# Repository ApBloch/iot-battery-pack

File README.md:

# iot-battery-pack
Design for a 3s iot battery pack with balance charging.

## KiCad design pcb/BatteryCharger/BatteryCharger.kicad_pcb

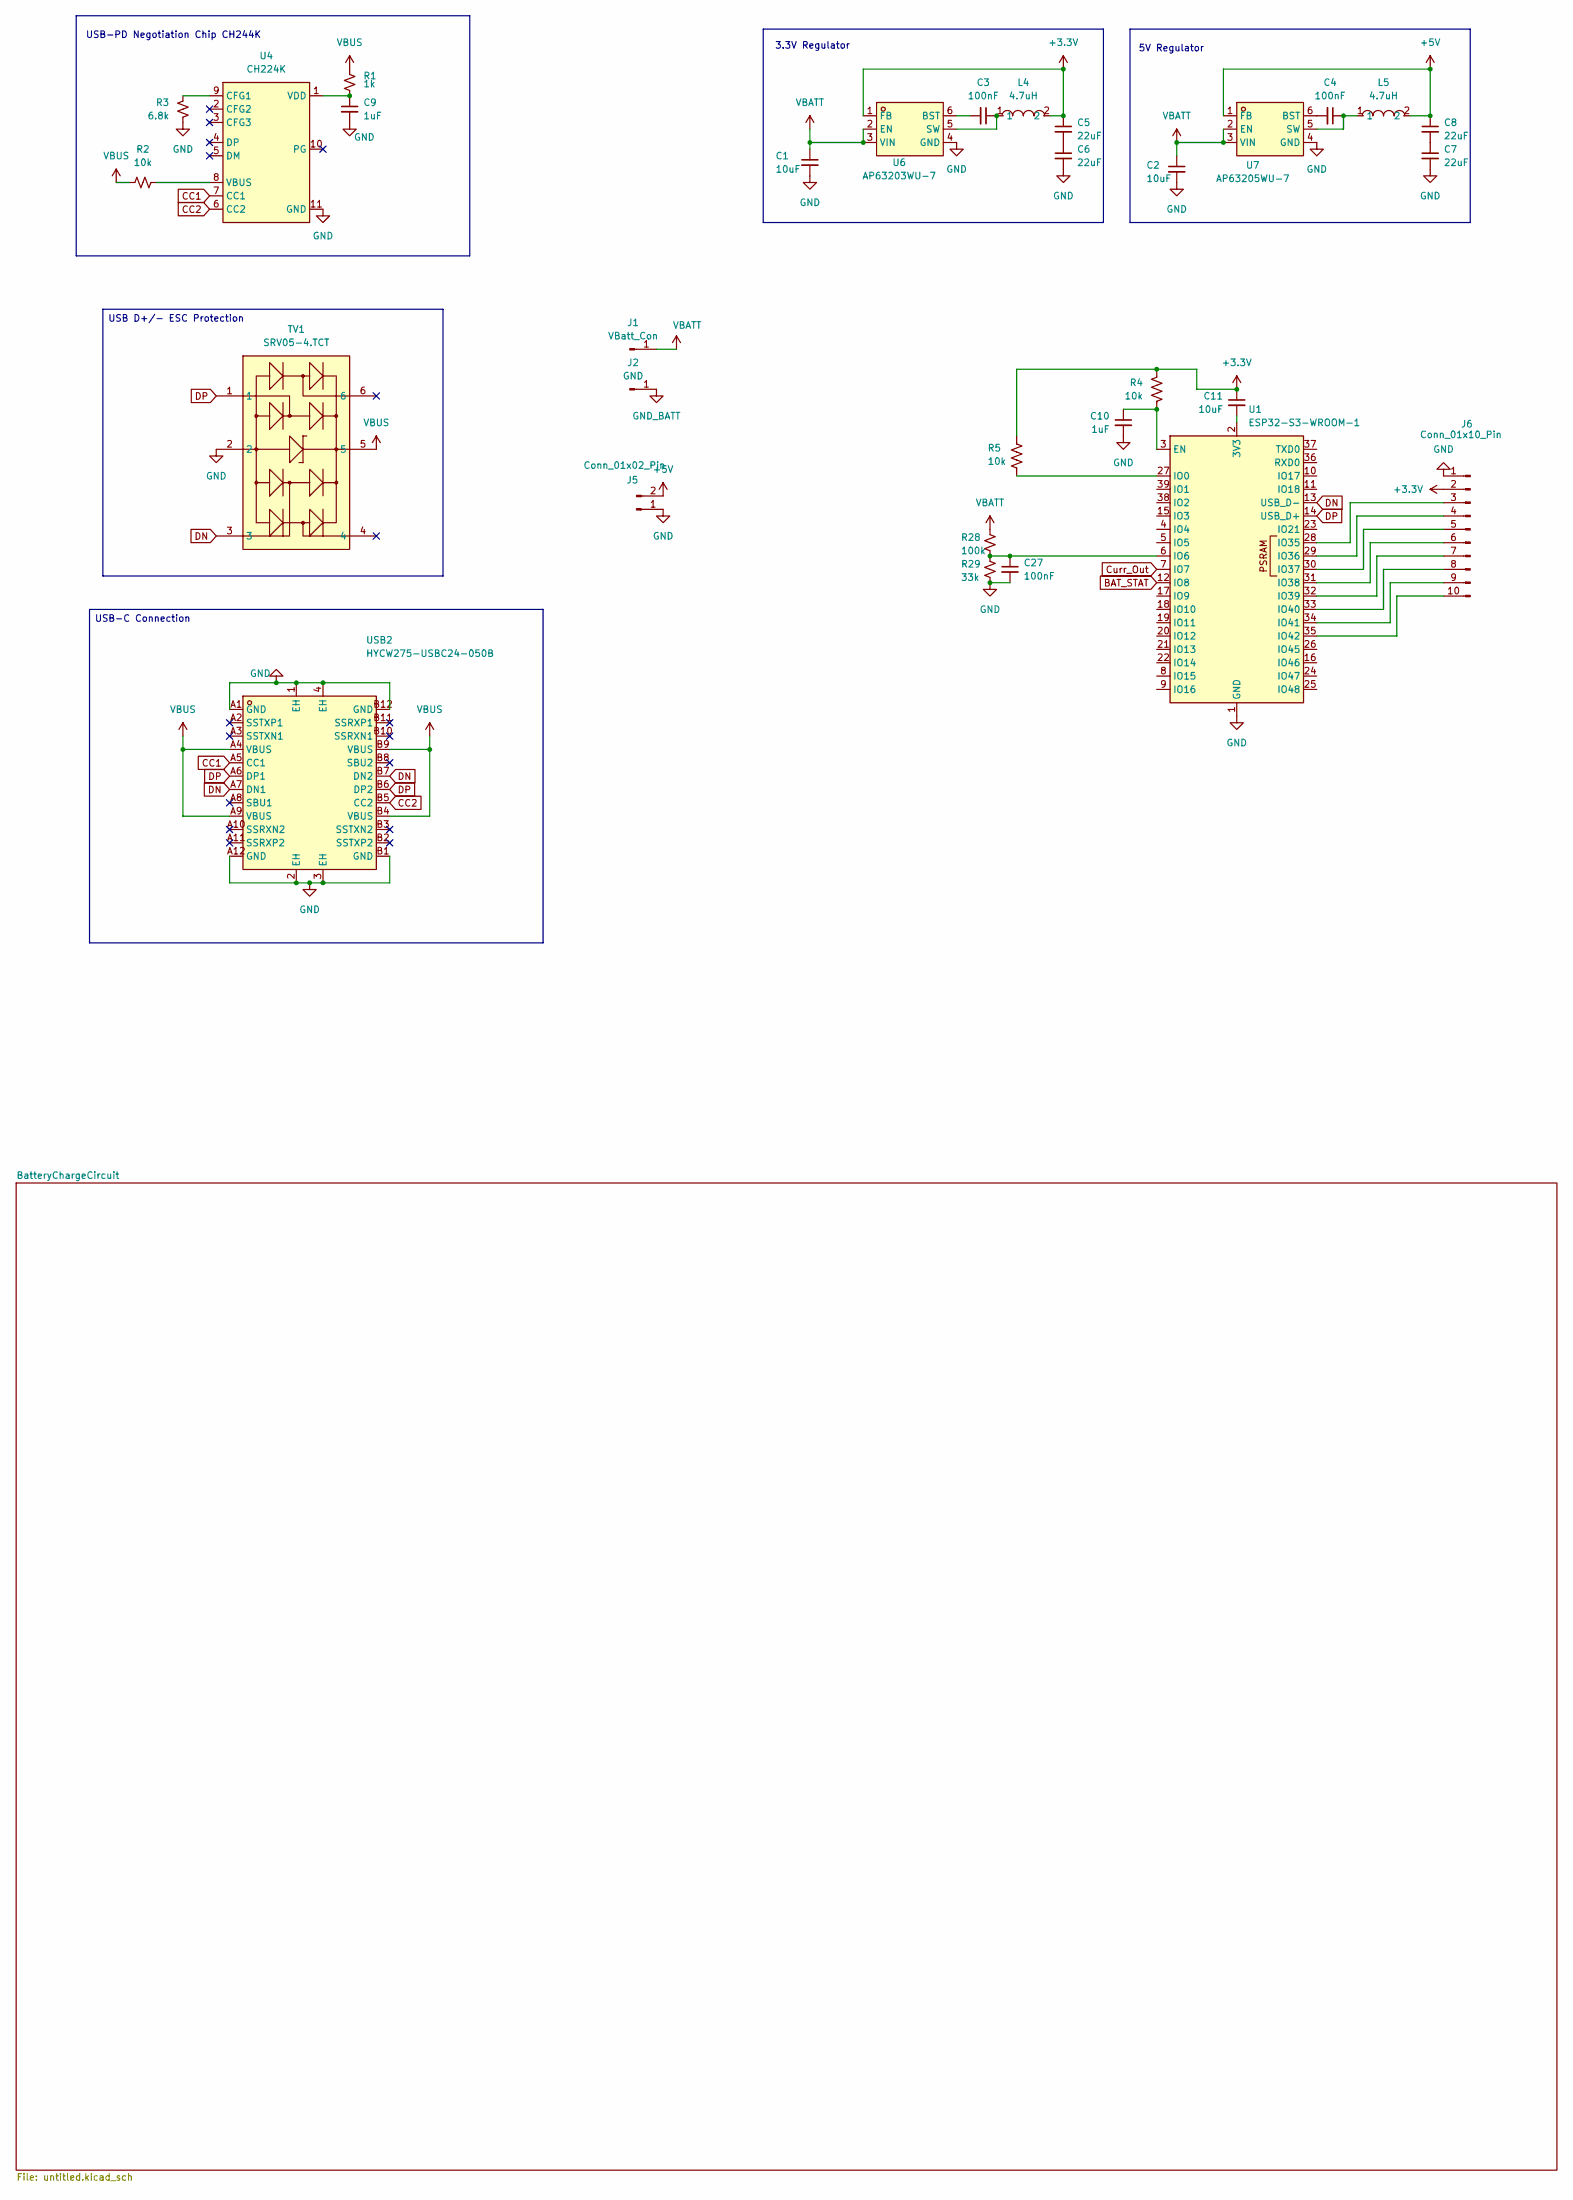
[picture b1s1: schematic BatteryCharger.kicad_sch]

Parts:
C1, C2, C11: 10uF; C_0603_1608Metric
C3, C4, C27: 100nF; C_0603_1608Metric
C5, C6, C7, C8: 22uF; C_0603_1608Metric
C9, C10: 1uF; C_0603_1608Metric
J1: VBatt_Con; TestPoint_THTPad_D4.0mm_Drill2.0mm
J2: GND; TestPoint_THTPad_4.0x4.0mm_Drill2.0mm
J5: Conn_01x02_Pin; PinHeader_1x02_P2.00mm_Vertical
J6: Conn_01x10_Pin; PinHeader_1x10_P2.54mm_Vertical
L4, L5: 4.7uH; IND-SMD_L5.7-W5.2_CYA0530; MPN CYA0520-4.7UH; LCSC Part C19274357
R1: 1k; R_0603_1608Metric
R2, R4, R5: 10k; R_0603_1608Metric
R3: 6.8k; R_0603_1608Metric
R28: 100k; R_0603_1608Metric
R29: 33k; R_0603_1608Metric
TV1: SRV05-4.TCT; SOT-23-6_L2.9-W1.6-P0.95-LS2.8-BR; MPN SRV05-4.TCT; LCSC Part C13612
U1: ESP32-S3-WROOM-1
U4: CH224K; ESSOP-10_L4.9-W3.9-P1.0-LS6.0-TL-EP; MPN CH224K; LCSC Part C970725
U6: AP63203WU-7; TSOT-26_L2.9-W1.6-P0.95-LS2.8-BL; MPN AP63203WU-7; LCSC Part C780769
U7: AP63205WU-7; TSOT-23-6_L2.9-W1.6-P0.95-LS2.8-BL; MPN AP63205WU-7; LCSC Part C2071056
USB2: HYCW275-USBC24-050B; USB-C-SMD_HYCW275-USBC24-050B; MPN HYCW275-USBC24-050B; LCSC Part C42400261

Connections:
+3.3V: C5.1, C11.1, J6.2, L4.2, R4.1, R5.1, U6.1 (FB); also elsewhere on the board
+5V: C8.1, J5.2, L5.2, U7.1 (FB)
BAT_STAT: U1.12 (IO8); also elsewhere on the board
CC1: U4.7 (CC1), USB2.A5 (CC1)
CC2: U4.6 (CC2), USB2.B5 (CC2)
Cell2_+: C1.1, C2.1, J1.1 (Pin_1_1), R28.1, U6.2 (EN), U6.3 (VIN), U7.2 (EN), U7.3 (VIN); also elsewhere on the board
Curr_Out: U1.7 (IO7); also elsewhere on the board
DN: TV1.3, U1.13 (USB_D-), USB2.A7 (DN1), USB2.B7 (DN2)
DP: TV1.1, U1.14 (USB_D+), USB2.A6 (DP1), USB2.B6 (DP2)
GND: C1.2, C2.2, C6.2, C7.2, C9.2, C10.2, C27.2, J5.1, J6.1, R3.2, R29.2, TV1.2, U1.1 (GND), U1.40 (GND), U1.41 (GND), U4.11 (GND), U6.4 (GND), U7.4 (GND), USB2.0, USB2.1 (EH), USB2.2 (EH), USB2.3 (EH), USB2.4 (EH), USB2.A1 (GND), USB2.A12 (GND), USB2.B1 (GND), USB2.B12 (GND); also elsewhere on the board
GND_BATT: J2.1 (Pin_1_1); also elsewhere on the board
unnamed: C5.2, C6.1
unnamed: C7.1, C8.2
unnamed: J6.3, U1.28 (IO35)
unnamed: J6.4, U1.29 (IO36)
unnamed: J6.5, U1.30 (IO37)
unnamed: J6.6, U1.31 (IO38)
unnamed: J6.7, U1.32 (IO39)
unnamed: J6.8, U1.33 (IO40)
unnamed: J6.9, U1.34 (IO41)
unnamed: J6.10, U1.35 (IO42)
unnamed: C11.2, U1.2 (3V3)
unnamed: C10.1, R4.2, U1.3 (EN)
unnamed: R5.2, U1.27 (IO0)
unnamed: C27.1, R28.2, R29.1, U1.6 (IO6)
unnamed: R3.1, U4.9 (CFG1)
unnamed: R2.1, U4.8 (VBUS)
unnamed: C9.1, R1.2, U4.1 (VDD)
unnamed: C3.2, U6.6 (BST)
unnamed: C3.1, L4.1, U6.5 (SW)
unnamed: C4.2, U7.6 (BST)
unnamed: C4.1, L5.1, U7.5 (SW)
VBUS: R1.1, R2.2, TV1.5, USB2.A4 (VBUS), USB2.A9 (VBUS), USB2.B4 (VBUS), USB2.B9 (VBUS); also elsewhere on the board

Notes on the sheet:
USB-PD Negotiation Chip CH244K
3.3V Regulator
5V Regulator
USB D+/- ESC Protection
USB-C Connection

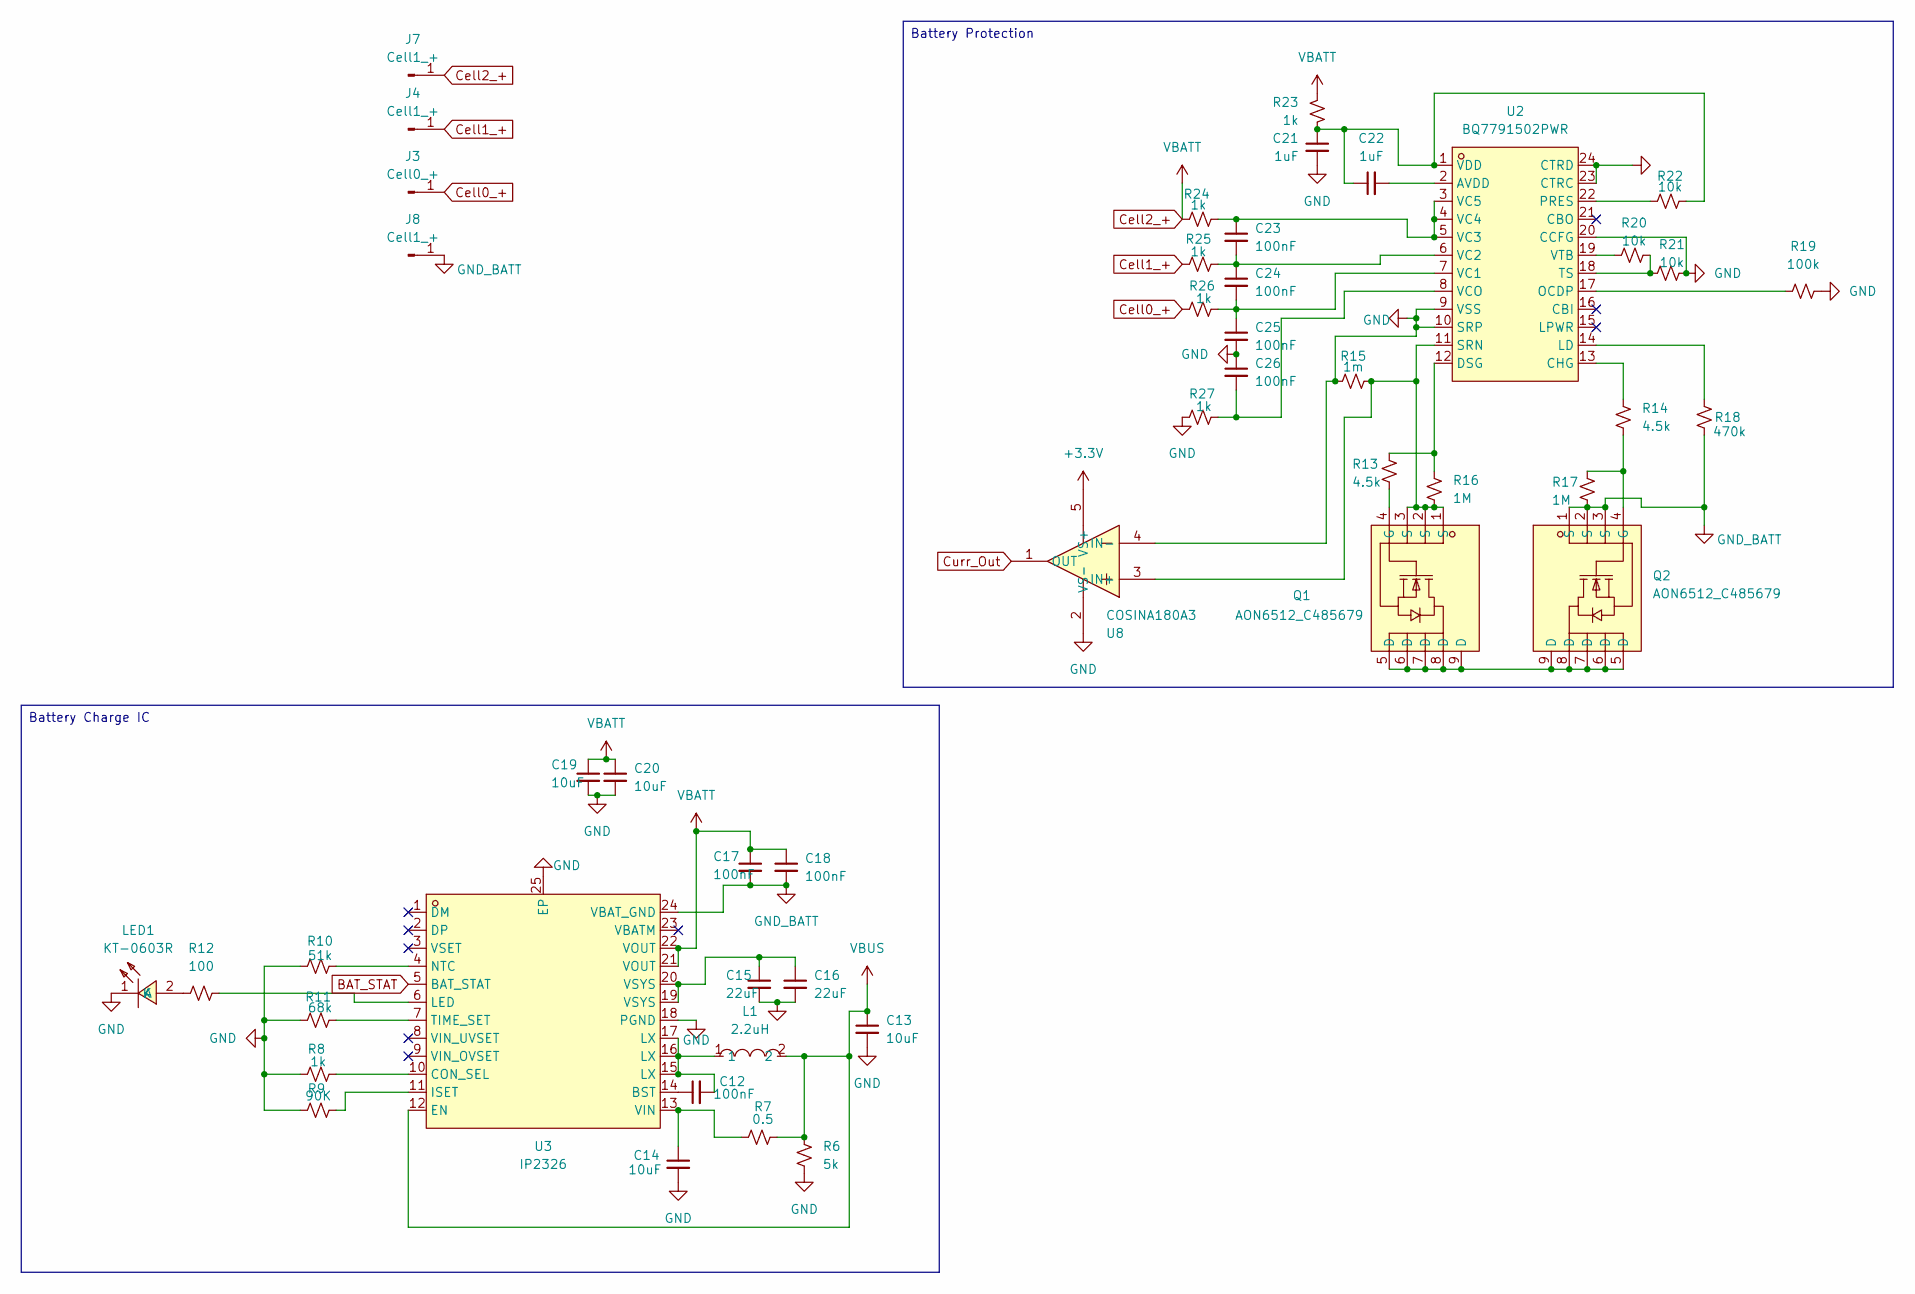
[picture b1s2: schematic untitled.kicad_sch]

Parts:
C12, C17, C18, C23, C24, C25, C26: 100nF; C_0603_1608Metric
C13, C14, C19, C20: 10uF; C_0603_1608Metric
C15, C16: 22uF; C_0603_1608Metric
C21, C22: 1uF; C_0603_1608Metric
J3: Cell0_+; TestPoint_Pad_D2.5mm
J4, J7, J8: Cell1_+; TestPoint_Pad_D2.5mm
L1: 2.2uH; IND-SMD_L5.0-W5.0; MPN CKCS5020-2.2uH/M; LCSC Part C354595
LED1: KT-0603R; LED0603-RD; MPN KT-0603R; LCSC Part C2286
Q1, Q2: AON6512_C485679; PDFN-8_L5.6-W5.2-P1.27-LS6.1-BL; MPN AON6512; LCSC Part C485679
R6: 5k; R_0603_1608Metric
R7: 0.5; R_0603_1608Metric
R8, R23, R24, R25, R26, R27: 1k; R_0603_1608Metric
R9: 90K; R_0603_1608Metric
R10: 51k; R_0603_1608Metric
R11: 68k; R_0603_1608Metric
R12: 100; R_0603_1608Metric
R13, R14: 4.5k; R_0603_1608Metric
R15: 1m; R_2512_6332Metric
R16, R17: 1M; R_0603_1608Metric
R18: 470k; R_0603_1608Metric
R19: 100k; R_0603_1608Metric
R20, R21, R22: 10k; R_0603_1608Metric
U2: BQ7791502PWR; TSSOP-24_L7.8-W4.4-P0.65-LS6.4-BL_1; MPN BQ7791502PWR; LCSC Part C2865574
U3: IP2326; VQFN-24_L4.0-W4.0-P0.50-BL-EP2.5; MPN IP2326; LCSC Part C2832094
U8: COSINA180A3; SOT-23-5_L2.9-W1.6-P0.95-LS2.8-BL; MPN COSINA180A3; LCSC Part C22392282

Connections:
+3.3V: U8.5 (VS+); also elsewhere on the board
BAT_STAT: U3.5 (BAT_STAT); also elsewhere on the board
Cell0_+: J3.1 (Pin_1_1), R26.1
Cell1_+: J4.1 (Pin_1_1), R25.1
Cell2_+: C17.1, C18.1, C19.1, C20.1, J7.1 (Pin_1_1), R23.1, R24.1, U3.21 (VOUT), U3.22 (VOUT); also elsewhere on the board
Curr_Out: U8.1 (OUT); also elsewhere on the board
GND: C13.2, C14.2, C15.2, C16.2, C19.2, C20.2, C21.2, C25.2, C26.1, LED1.1 (K), R6.2, R8.1, R9.1, R10.1, R11.1, R15.1, R19.2, R21.2, R27.1, U2.9 (VSS), U2.10 (SRP), U2.20 (CCFG), U2.23 (CTRC), U2.24 (CTRD), U3.18 (PGND), U3.25 (EP), U8.2 (VS-), U8.4 (IN-); also elsewhere on the board
GND_BATT: C17.2, C18.2, J8.1 (Pin_1_1), Q2.1 (S), Q2.2 (S), Q2.3 (S), R17.2, R18.1, U3.24 (VBAT_GND); also elsewhere on the board
unnamed: C12.2, L1.1, U3.15 (LX), U3.16 (LX), U3.17 (LX)
unnamed: C15.1, C16.1, U3.19 (VSYS), U3.20 (VSYS)
unnamed: LED1.2 (A), R12.1
unnamed: Q1.5 (D), Q1.6 (D), Q1.7 (D), Q1.8 (D), Q1.9 (D), Q2.5 (D), Q2.6 (D), Q2.7 (D), Q2.8 (D), Q2.9 (D)
unnamed: Q1.4 (G), R13.2
unnamed: Q2.4 (G), R14.2, R17.1
unnamed: C22.2, U2.2 (AVDD)
unnamed: R14.1, U2.13 (CHG)
unnamed: R13.1, R16.1, U2.12 (DSG)
unnamed: R18.2, U2.14 (LD)
unnamed: R19.1, U2.17 (OCDP)
unnamed: R22.1, U2.22 (PRES)
unnamed: Q1.1 (S), Q1.2 (S), Q1.3 (S), R15.2, R16.2, U2.11 (SRN), U8.3 (IN+)
unnamed: R20.2, R21.1, U2.18 (TS)
unnamed: C24.2, C25.1, R26.2, U2.7 (VC1)
unnamed: C23.2, C24.1, R25.2, U2.6 (VC2)
unnamed: C23.1, R24.2, U2.3 (VC5), U2.4 (VC4), U2.5 (VC3)
unnamed: C26.2, R27.2, U2.8 (VCO)
unnamed: C21.1, C22.1, R22.2, R23.2, U2.1 (VDD)
unnamed: R20.1, U2.19 (VTB)
unnamed: C12.1, U3.14 (BST)
unnamed: R8.2, U3.10 (CON_SEL)
unnamed: R9.2, U3.11 (ISET)
unnamed: R12.2, U3.6 (LED)
unnamed: R10.2, U3.4 (NTC)
unnamed: R11.2, U3.7 (TIME_SET)
unnamed: C14.1, R7.1, U3.13 (VIN)
VBUS: C13.1, L1.2, R6.1, R7.2, U3.12 (EN); also elsewhere on the board

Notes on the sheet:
Battery Protection
Battery Charge IC

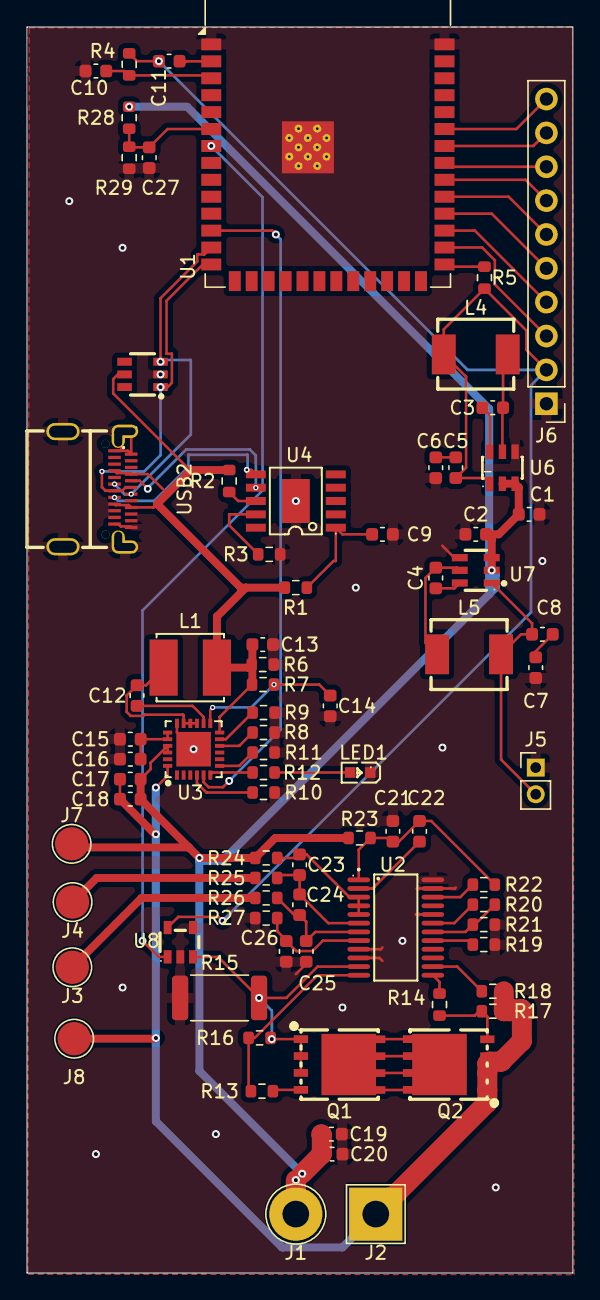
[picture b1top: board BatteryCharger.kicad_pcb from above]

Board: 2 copper layers, 41.0 x 93.5 mm, 79 parts (0 on the bottom side), 62 nets.
